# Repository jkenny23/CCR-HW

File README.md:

# CCR v2.5su
Board/schematic/gerber files for the CCR project - v2.5su variant

This variant is the latest (as of 5/6/20) cost optimized version, which supports regen automatically, with use of external buffer pack (clamp circuit limits voltage at input of tester to 12.5V). All specs are the same as v2.4 otherwise (6A charge/discharge symmetric, thermally limited to 21W max without buffer pack). Fixed 2 errors in the v2.4su version, moving TL431 supply to 12V instead of 5V (delay in powering reference caused clamp circuit to engage, shorting power supply if USB power was not provided first), and adding diode to 5V SMPS (MP2359 is a non-synchronous buck whereas v2.4 JW5052C was).

Details here: http://rev0.net/index.php?title=CCR

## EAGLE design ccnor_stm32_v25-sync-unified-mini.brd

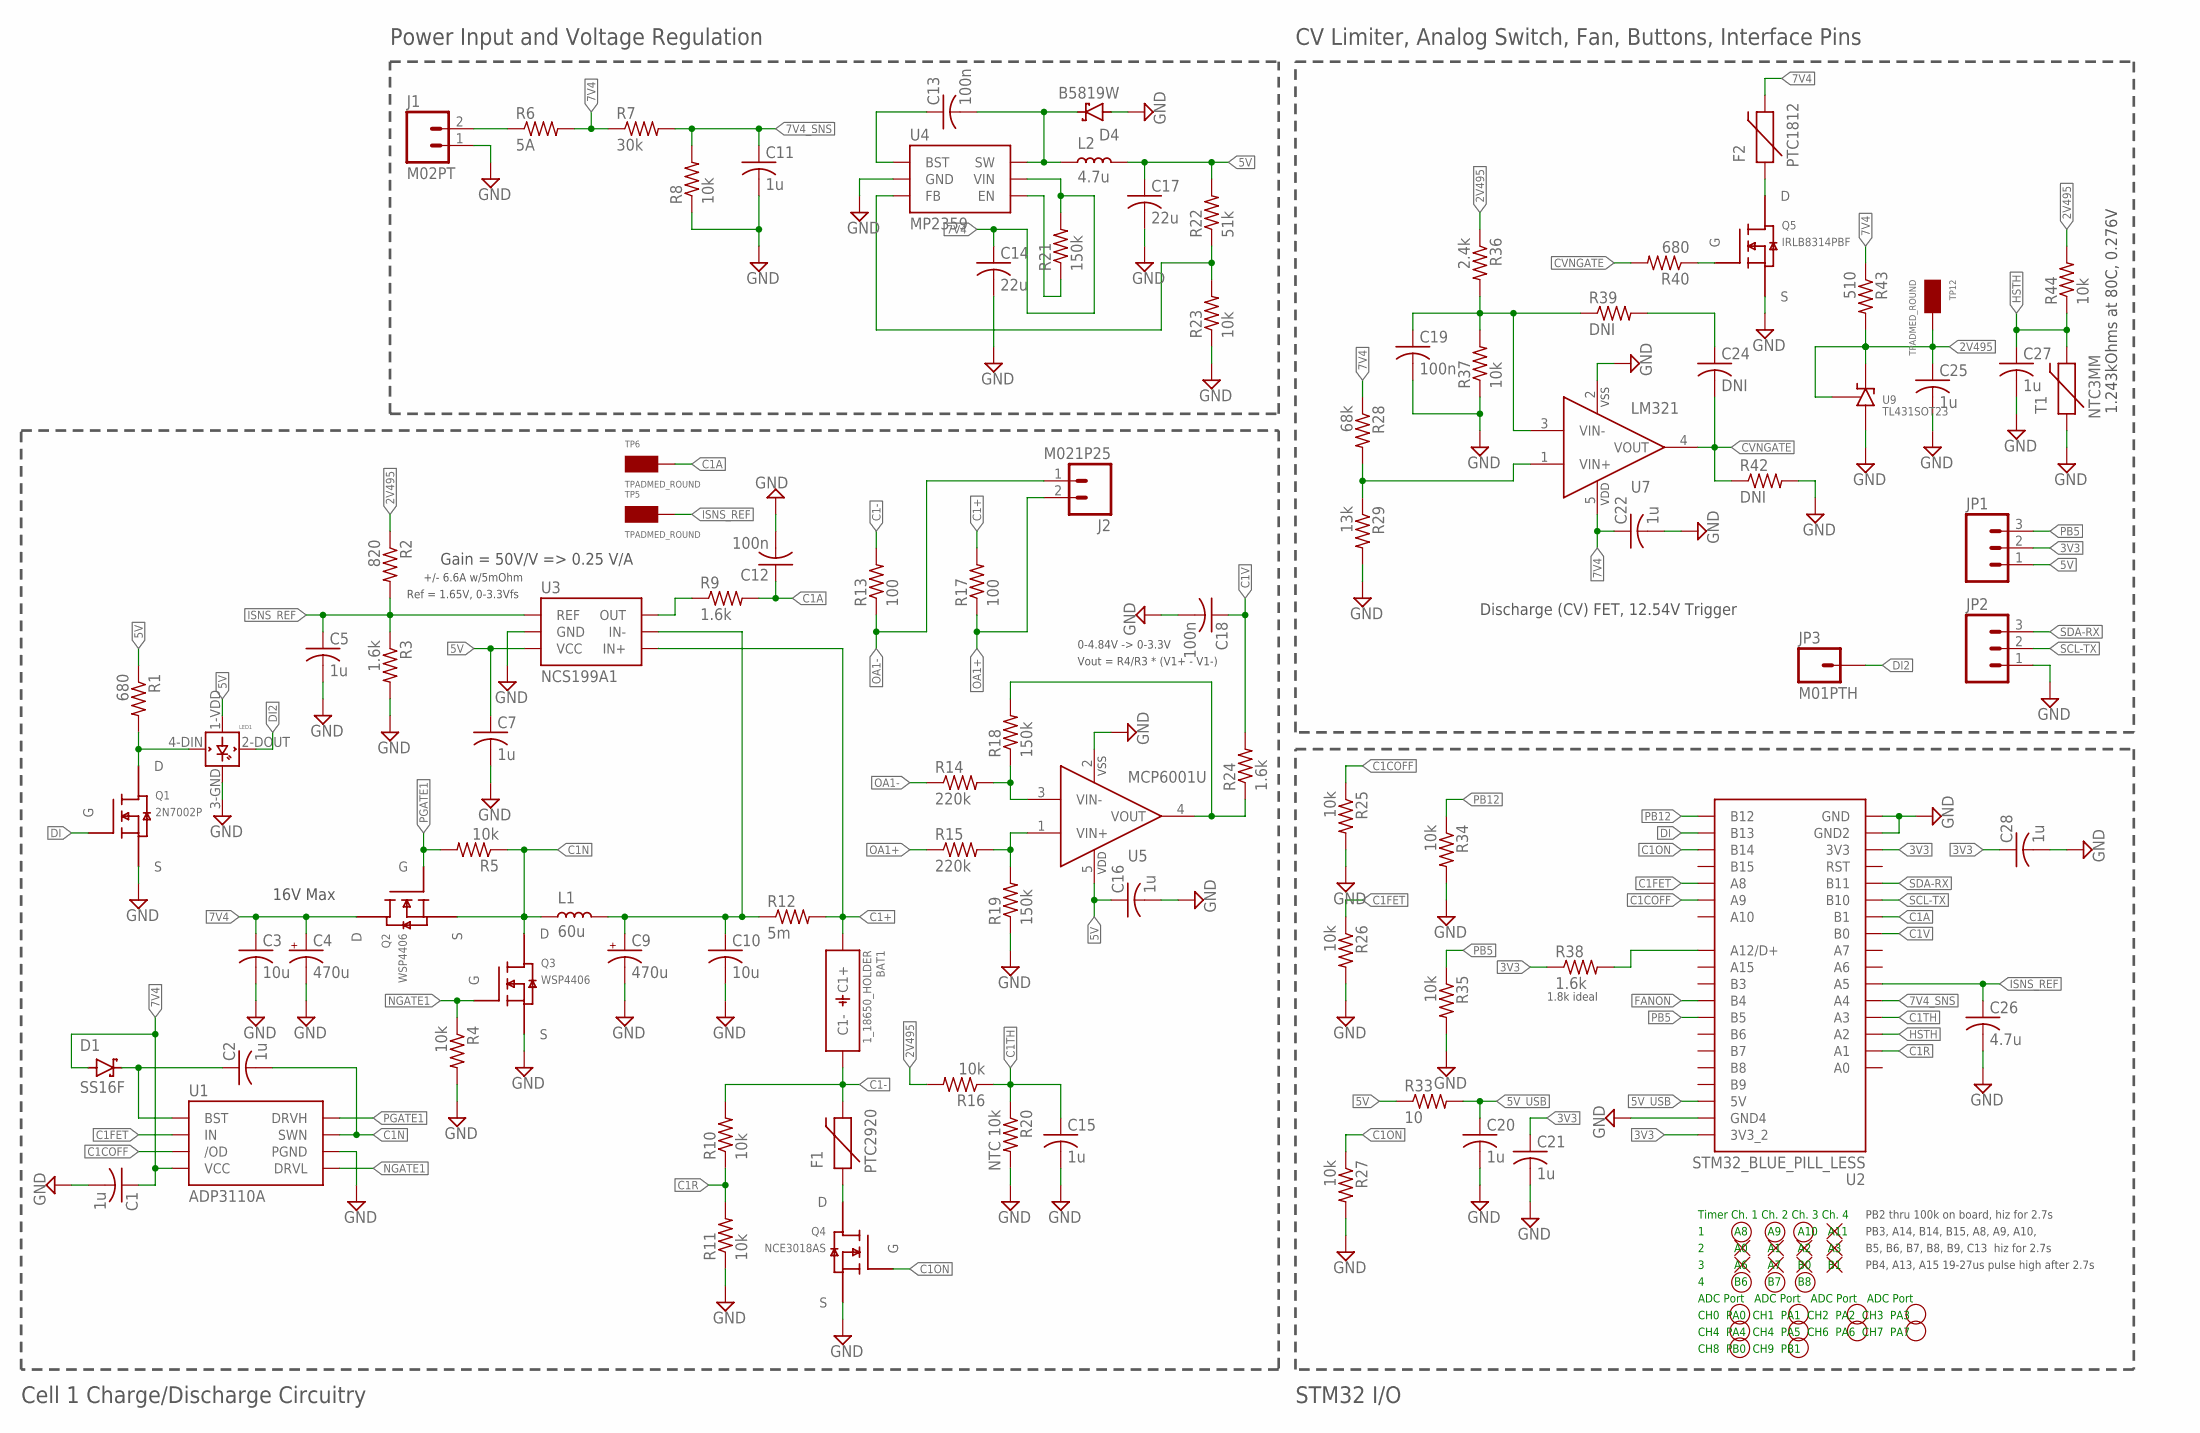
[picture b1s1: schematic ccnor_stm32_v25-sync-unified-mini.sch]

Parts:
BAT1: 1_18650_HOLDER; 1S_18650_SMD_NH
C1, C5, C7, C11, C15, C16, C20, C21, C22, C25, C27, C28: 1u; C0402
C2: 1u; C0603
C3, C10: 10u; C1206
C4, C9: 470u; E2,5-7
C12, C13, C18, C19: 100n; C0402
C14: 22u; C0805
C17: 22u; C0603
C24: DNI; C0402
C26: 4.7u; C0402
D1: SS16F; SOD123
D4: B5819W; SOD123W
F1: PTC2920; 2920
F2: PTC1812; 1812
J1: M02PT; PHOENIXCONTACT1935161
J2: M021P25; M02_1P25MM
JP1, JP2: M03PTH; 1X03
JP3: M01PTH; 1X01
L1: 60u; INDUCTOR_10A_8.2MMX21MM
L2: 4.7u; 0805
LED1: WS2812B
Q1: 2N7002P; SOT23
Q2, Q3: WSP4406; 8-SOIC
Q4: NCE3018AS; 8-SOIC
Q5: IRLB8314PBF; TO-220
R1, R40: 680; R0402
R2: 820; R0402
R3, R9, R24, R38: 1.6k; R0402
R4, R5, R8, R10, R11, R16, R23, R25, R26, R27, R34, R35, R37, R44: 10k; R0402
R6: 5A; R1206
R7: 30k; R0402
R12: 5m; R1206
R13, R17: 100; R0402
R14, R15: 220k; R0402
R18, R19, R21: 150k; R0402
R20: NTC 10k; R0402
R22: 51k; R0402
R28: 68k; R0402
R29: 13k; R0402
R33: 10; R0402
R36: 2.4k; R0402
R39, R42: DNI; R0402
R43: 510; R0402
T1: NTC3MM; THERMISTOR_3MMX3MM
TP5, TP6, TP12: TPADMED_ROUND; TPAD_MED_ROUND
U1: ADP3110A; 8-SOIC
U2: STM32_BLUE_PILL_LESS; STM32_BLUE_PILL_SMD
U3: NCS199A1; SOT-363
U4: MP2359; SOT23-6
U5: MCP6001U; SOT23-5
U7: LM321; SOT23-5
U9: TL431SOT23; SOT23

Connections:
2V495: C25.1, R2.1, R16.2, R36.1, R43.2, R44.2, TP12.1, U9.1 (K), U9.2 (REF)
3V3: C21.1, C28.1, JP1.2, R38.1, U2.3V3, U2.3V3_2
5V: C7.1, C16.1, C17.1, JP1.1, L2.2, LED1.1-VDD (VDD), R1.1, R22.2, R33.1, U3.3 (VCC), U5.5 (VDD)
5V_USB: C20.1, R33.2, U2.5V
7V4: C1.1, C3.1, C4.+, C14.1, C22.1, D1.A (ANODE), F2.2, Q2.5 (D), Q2.6 (D), Q2.7 (D), Q2.8 (D), R6.2, R7.1, R21.2, R28.1, R43.1, U1.4 (VCC), U4.5 (VIN), U7.5 (VDD)
7V4_SNS: C11.1, R7.2, R8.2, U2.A4
BST: C2.1, D1.K (CATHODE), U1.1 (BST)
BST5V: C13.1, U4.1 (BST)
C1+: BAT1.1+ (C1+), R12.2, R17.2, U3.4 (IN+)
C1-: BAT1.1- (C1-), F1.K (2), R10.2, R13.2
C1A: C12.1, R9.2, TP6.1, U2.B1
C1COFF: R25.1, U1.3 (/OD), U2.A9
C1FET: R26.1, U1.2 (IN), U2.A8
C1N: C2.2, L1.P$1, Q2.1 (S), Q2.2 (S), Q2.3 (S), Q3.5 (D), Q3.6 (D), Q3.7 (D), Q3.8 (D), R5.1, U1.7 (SWN)
C1ON: Q4.4 (G), R27.1, U2.B14
C1R: R10.1, R11.2, U2.A1
C1TH: C15.1, R16.1, R20.1, U2.A3
C1V: C18.1, R24.2, U2.B0
C1VFBN: C24.1, R39.2
C1V_OA: R18.2, R24.1, U5.4 (VOUT)
CVNGATE: C24.2, R40.2, R42.1, U7.4 (VOUT)
CVOAREF: C19.1, R36.2, R37.2, R39.1, U7.3 (VIN-)
CVOASNS: R28.2, R29.1, U7.1 (VIN+)
DI: Q1.1 (G), U2.B13
DI1: LED1.4-DIN (DIN), Q1.3 (D), R1.2
DI2: JP3.1, LED1.2-DOUT (DOUT)
EN5V: R21.1, U4.4 (EN)
FANON: U2.B4
FB5V: R22.1, R23.2, U4.3 (FB)
GND: C1.2, C3.2, C4.-, C5.2, C7.2, C9.-, C10.2, C11.2, C12.2, C14.2, C15.2, C16.2, C17.2, C18.2, C19.2, C20.2, C21.2, C22.2, C25.2, C26.2, C27.2, C28.2, D4.A (ANODE), J1.1, JP2.1, LED1.3-GND (GND), Q1.2 (S), Q3.1 (S), Q3.2 (S), Q3.3 (S), Q4.1 (S), Q4.2 (S), Q4.3 (S), Q5.3 (S), R3.2, R4.2, R8.1, R11.1, R19.1, R20.2, R23.1, R25.2, R26.2, R27.2, R29.2, R34.2, R35.2, R37.1, R42.2, T1.1, U1.6 (PGND), U2.GND, U2.GND2, U2.GND4, U3.2 (GND), U4.2 (GND), U5.2 (VSS), U7.2 (VSS), U9.3 (A)
HSTH: C27.1, R44.1, T1.2, U2.A2
IN-1: C9.+, C10.1, L1.P$2, R12.1, U3.5 (IN-)
IS1O: R9.1, U3.6 (OUT)
ISNS_REF: C5.1, C26.1, R2.2, R3.1, TP5.1, U2.A5, U3.1 (REF)
unnamed: R15.2, R19.2, U5.1 (VIN+)
unnamed: R14.2, R18.1, U5.3 (VIN-)
unnamed: F2.1, Q5.2 (D)
unnamed: J1.2, R6.1
unnamed: R38.2, U2.A12 (A12/D+)
unnamed: F1.A (1), Q4.5 (D), Q4.6 (D), Q4.7 (D), Q4.8 (D)
NGATE1: Q3.4 (G), R4.1, U1.5 (DRVL)
OA1+: J2.2, R15.1, R17.1
OA1-: J2.1, R13.1, R14.1
PB5: JP1.3, R35.1, U2.B5
PB12: R34.1, U2.B12
PGATE1: Q2.4 (G), R5.2, U1.8 (DRVH)
Q7G: Q5.1 (G), R40.1
SCL-TX: JP2.2, U2.B10
SDA-RX: JP2.3, U2.B11
SW5V: C13.2, D4.K (CATHODE), L2.1, U4.6 (SW)

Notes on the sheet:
Gain = 50V/V => 0.25 V/A
Ref = 1.65V, 0-3.3Vfs
+/- 6.6A w/5mOhm
Vout = R4/R3 * (V1+ - V1-)
0-4.84V -> 0-3.3V
16V Max
STM32 I/O
Discharge (CV) FET, 12.54V Trigger
Timer Ch. 1 Ch. 2 Ch. 3 Ch. 4
1 A8 A9 A10 A11
2 A0 A1 A2 A3
3 A6 A7 B0 B1
4 B6 B7 B8
ADC Port ADC Port ADC Port ADC Port
CH0 PA0 CH1 PA1 CH2 PA2 CH3 PA3
CH4 PA4 CH4 PA5 CH6 PA6 CH7 PA7
CH8 PB0 CH9 PB1
PB2 thru 100k on board, hiz for 2.7s
PB3, A14, B14, B15, A8, A9, A10,
PB4, A13, A15 19-27us pulse high after 2.7s
B5, B6, B7, B8, B9, C13 hiz for 2.7s
1.243kOhms at 80C, 0.276V
Cell 1 Charge/Discharge Circuitry
CV Limiter, Analog Switch, Fan, Buttons, Interface Pins
1.8k ideal
Power Input and Voltage Regulation

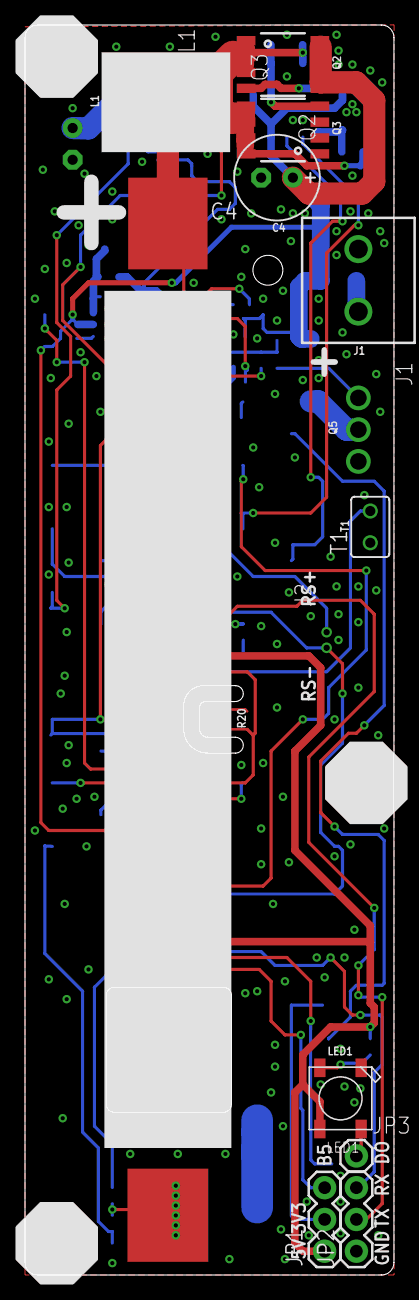
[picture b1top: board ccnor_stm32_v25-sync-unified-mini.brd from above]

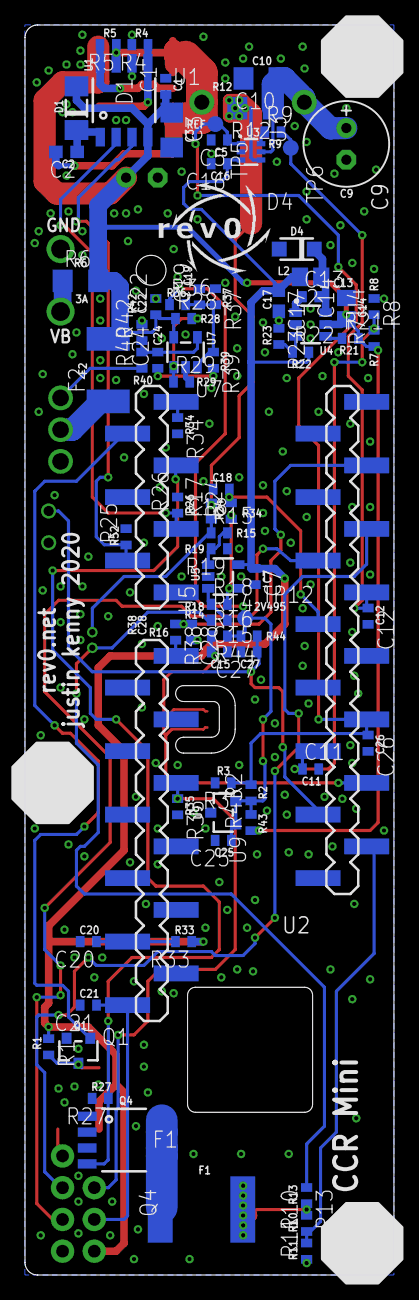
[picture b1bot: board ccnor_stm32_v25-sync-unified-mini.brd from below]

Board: 2 copper layers, 29.5 x 100.0 mm, 94 parts (80 on the bottom side), 49 nets.

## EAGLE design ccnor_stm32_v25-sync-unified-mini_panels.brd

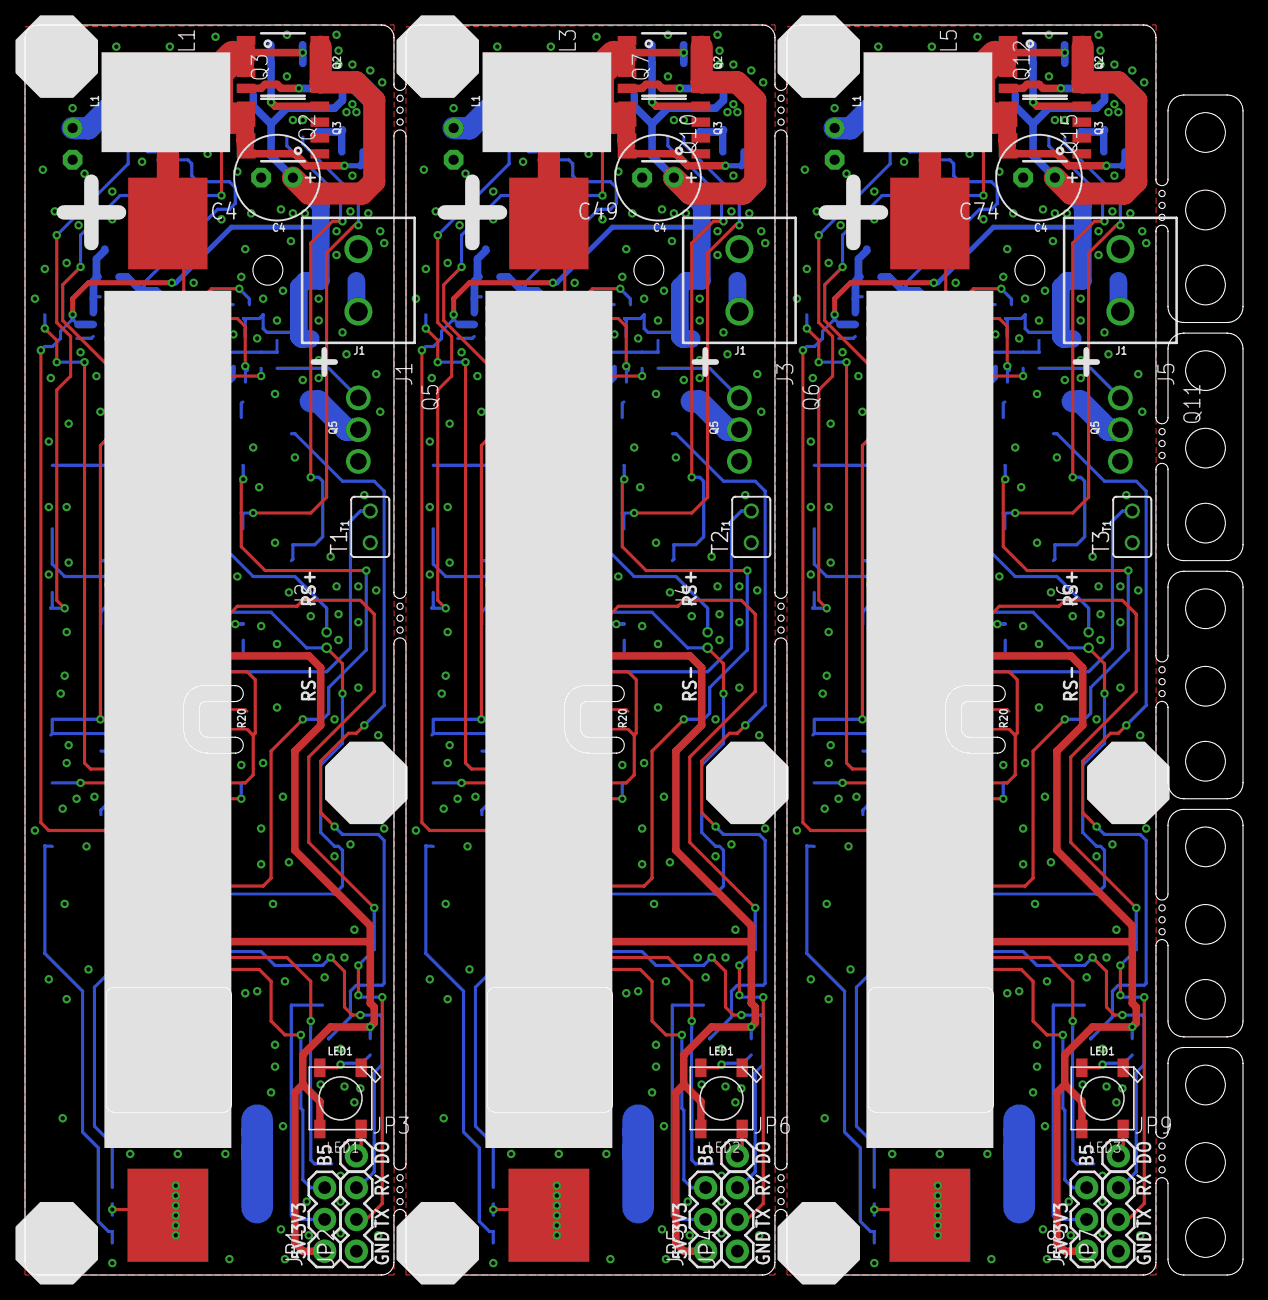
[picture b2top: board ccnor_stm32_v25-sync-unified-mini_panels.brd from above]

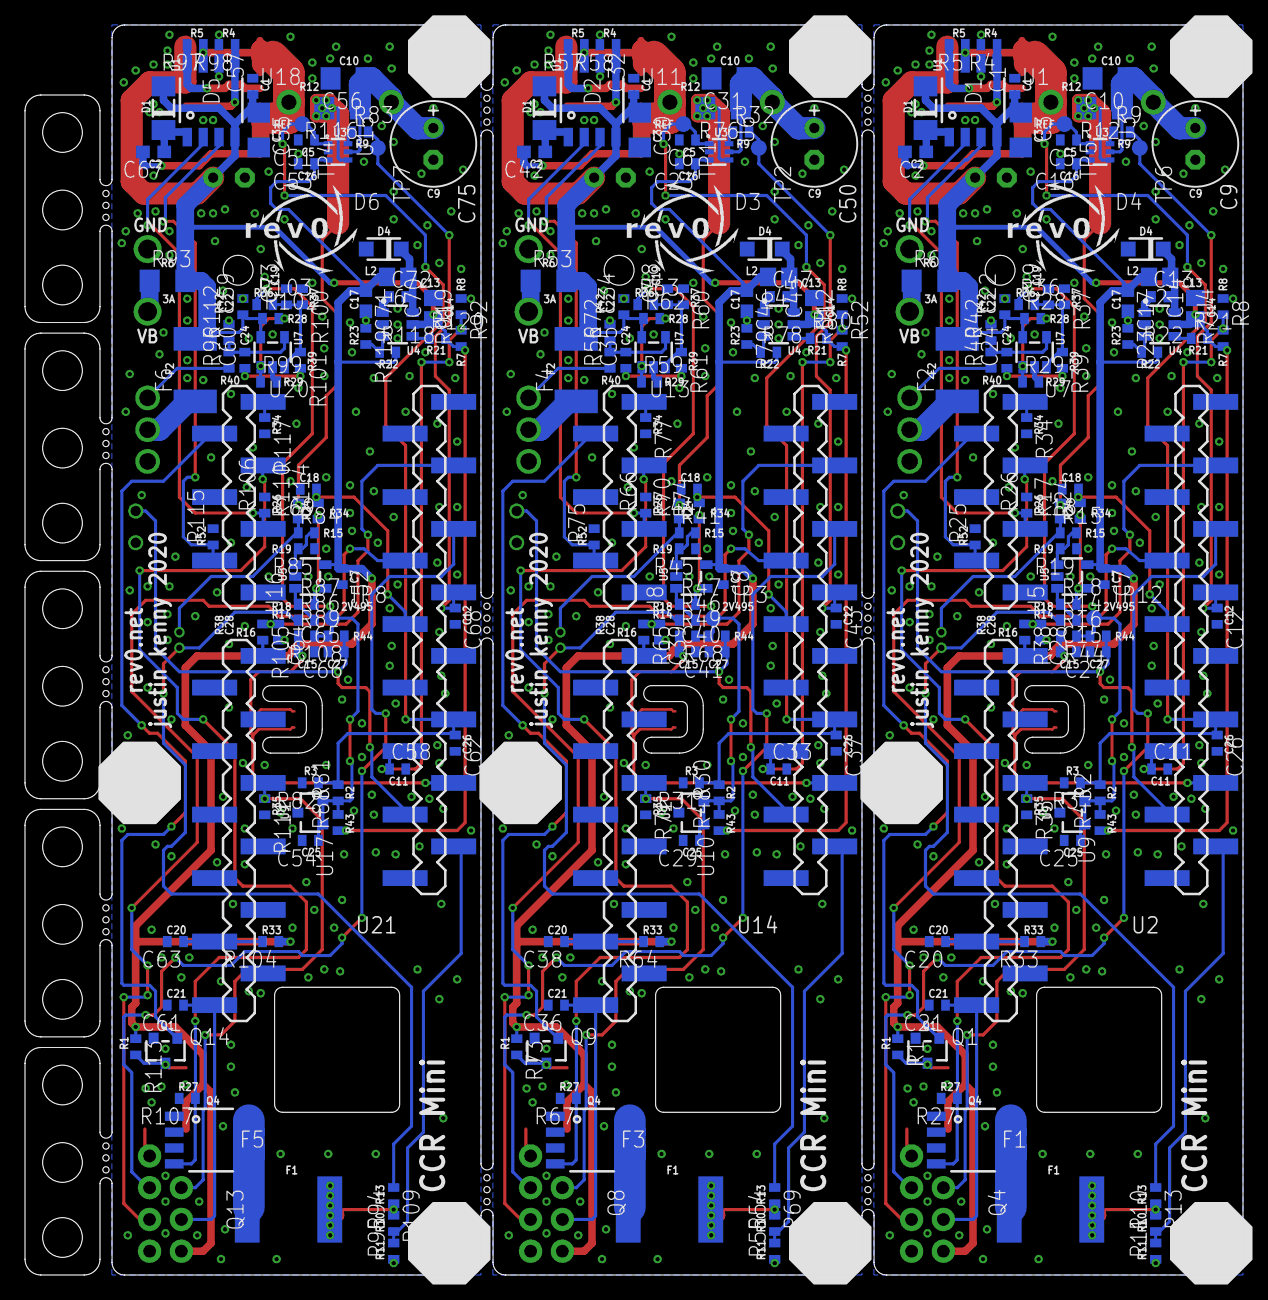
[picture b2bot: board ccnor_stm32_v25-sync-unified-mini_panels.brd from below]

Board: 2 copper layers, 97.4 x 100.0 mm, 282 parts (240 on the bottom side), 147 nets.

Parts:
BAT1, BAT2, BAT3: 1_18650_HOLDER; 1S_18650_SMD_NH
C1, C5, C6, C7, C8, C11, C15, C16, C20, C21, C22, C23, C25, C27, C28, C29, C32, C33, C34, C36, C38, C39, C40, C41, C51, C52, C53, C54, C57, C58, C59, C61, C63, C64, C65, C66: 1u; C0402
C2, C42, C67: 1u; C0603
C3, C10, C30, C31, C55, C56: 10u; C1206
C4, C9, C49, C50, C74, C75: 470u; E2,5-7
C12, C13, C18, C19, C43, C44, C47, C48, C68, C69, C72, C73: 100n; C0402
C14, C45, C70: 22u; C0805
C17, C46, C71: 22u; C0603
C24, C35, C60: DNI; C0402
C26, C37, C62: 4.7u; C0402
D1, D2, D5: SS16F; SOD123
D3, D4, D6: B5819W; SOD123W
F1, F3, F5: PTC2920; 2920
F2, F4, F6: PTC1812; 1812
J1, J3, J5: M02PT; PHOENIXCONTACT1935161
J2, J4, J6: M021P25; M02_1P25MM
JP1, JP2, JP4, JP5, JP7, JP8: 1X03
JP3, JP6, JP9: M01PTH; 1X01
L1, L3, L5: 60u; INDUCTOR_10A_8.2MMX21MM
L2, L4, L6: 4.7u; 0805
LED1, LED2, LED3: WS2812B
Q1, Q9, Q14: 2N7002P; SOT23
Q2, Q3, Q7, Q10, Q12, Q15: WSP4406; 8-SOIC
Q4, Q8, Q13: NCE3018AS; 8-SOIC
Q5, Q6, Q11: IRLB8314PBF; TO-220
R1, R40, R56, R73, R96, R113: 680; R0402
R2, R30, R81: 820; R0402
R3, R9, R24, R31, R32, R38, R65, R74, R82, R83, R105, R114: 1.6k; R0402
R4, R5, R8, R10, R11, R16, R23, R25, R26, R27, R34, R35, R37, R44, R49, R52, R54, R55, R57, R58, R60, R66, R67, R68, R71, R75, R77, R79, R89, R92, R94, R95, R97, R98, R100, R106, R107, R108, R111, R115, R117, R119: 10k; R0402
R6, R53, R93: 5A; R1206
R7, R51, R91: 30k; R0402
R12, R76, R116: 5m; R1206
R13, R17, R69, R70, R109, R110: 100; R0402
R14, R15, R41, R46, R84, R86: 220k; R0402
R18, R19, R21, R45, R47, R80, R85, R87, R120: 150k; R0402
R20, R50, R90: NTC 10k; R0402
R22, R78, R118: 51k; R0402
R28, R62, R102: 68k; R0402
R29, R59, R99: 13k; R0402
R33, R64, R104: 10; R0402
R36, R63, R103: 2.4k; R0402
R39, R42, R61, R72, R101, R112: DNI; R0402
R43, R48, R88: 510; R0402
T1, T2, T3: NTC3MM; THERMISTOR_3MMX3MM
TP1, TP2, TP3, TP4, TP5, TP6, TP7, TP8, TP12: TPADMED_ROUND; TPAD_MED_ROUND
U1, U11, U18: ADP3110A; 8-SOIC
U2, U14, U21: STM32_BLUE_PILL_LESS; STM32_BLUE_PILL_SMD
U3, U6, U15: NCS199A1; SOT-363
U4, U12, U19: MP2359; SOT23-6
U5, U8, U16: MCP6001U; SOT23-5
U7, U13, U20: LM321; SOT23-5
U9, U10, U17: TL431SOT23; SOT23

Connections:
2V1: C29.1, R30.1, R48.2, R49.2, R63.1, R68.2, TP3.1, U10.1, U10.2
2V2: C54.1, R81.1, R88.2, R89.2, R103.1, R108.2, TP8.1, U17.1, U17.2
2V495: C25.1, R2.1, R16.2, R36.1, R43.2, R44.2, TP12.1, U9.1, U9.2
3V1: C36.1, C39.1, JP5.2, R65.1, U14.3V3, U14.3V3_2
3V2: C61.1, C64.1, JP8.2, R105.1, U21.3V3, U21.3V3_2
3V3: C21.1, C28.1, JP1.2, R38.1, U2.3V3, U2.3V3_2
5V: C7.1, C16.1, C17.1, JP1.1, L2.2, LED1.1-VDD, R1.1, R22.2, R33.1, U3.3, U5.5
5V1: C8.1, C23.1, C46.1, JP5.1, L4.2, LED2.1-VDD, R64.1, R73.1, R78.2, U6.3, U8.5
5V2: C52.1, C53.1, C71.1, JP8.1, L6.2, LED3.1-VDD, R104.1, R113.1, R118.2, U15.3, U16.5
5V_USB: C20.1, R33.2, U2.5V
5V_USB1: C38.1, R64.2, U14.5V
5V_USB2: C63.1, R104.2, U21.5V
7V1: C30.1, C32.1, C34.1, C45.1, C49.+, D2.A, F4.2, Q10.5, Q10.6, Q10.7, Q10.8, R48.1, R51.1, R53.2, R62.1, R80.2, U11.4, U12.5, U13.5
7V2: C55.1, C57.1, C59.1, C70.1, C74.+, D5.A, F6.2, Q15.5, Q15.6, Q15.7, Q15.8, R88.1, R91.1, R93.2, R102.1, R120.2, U18.4, U19.5, U20.5
7V4: C1.1, C3.1, C4.+, C14.1, C22.1, D1.A, F2.2, Q2.5, Q2.6, Q2.7, Q2.8, R6.2, R7.1, R21.2, R28.1, R43.1, U1.4, U4.5, U7.5
7V4_SNS: C11.1, R7.2, R8.2, U2.A4
7V4_SNS1: C33.1, R51.2, R52.2, U14.A4
7V4_SNS2: C58.1, R91.2, R92.2, U21.A4
BST: C2.1, D1.K, U1.1
BST1: C42.1, D2.K, U11.1
BST2: C67.1, D5.K, U18.1
BST5V: C13.1, U4.1
BST5V1: C47.1, U12.1
BST5V2: C72.1, U19.1
C1+: BAT1.1+, R12.2, R17.2, U3.4
C1+1: BAT2.1+, R70.2, R76.2, U6.4
C1+2: BAT3.1+, R110.2, R116.2, U15.4
C1-: BAT1.1-, F1.K, R10.2, R13.2
C1-1: BAT2.1-, F3.K, R54.2, R69.2
C1-2: BAT3.1-, F5.K, R94.2, R109.2
C1A: C12.1, R9.2, TP6.1, U2.B1
C1A1: C43.1, R32.2, TP2.1, U14.B1
C1A2: C68.1, R83.2, TP7.1, U21.B1
C1COFF: R25.1, U1.3, U2.A9
C1COFF1: R75.1, U11.3, U14.A9
C1COFF2: R115.1, U18.3, U21.A9
C1FET: R26.1, U1.2, U2.A8
C1FET1: R66.1, U11.2, U14.A8
C1FET2: R106.1, U18.2, U21.A8
C1N: C2.2, L1.P$1, Q2.1, Q2.2, Q2.3, Q3.5, Q3.6, Q3.7, Q3.8, R5.1, U1.7
C1N1: C42.2, L3.P$1, Q7.5, Q7.6, Q7.7, Q7.8, Q10.1, Q10.2, Q10.3, R57.1, U11.7
C1N2: C67.2, L5.P$1, Q12.5, Q12.6, Q12.7, Q12.8, Q15.1, Q15.2, Q15.3, R97.1, U18.7
C1ON: Q4.4, R27.1, U2.B14
C1ON1: Q8.4, R67.1, U14.B14
C1ON2: Q13.4, R107.1, U21.B14
C1R: R10.1, R11.2, U2.A1
C1R1: R54.1, R55.2, U14.A1
C1R2: R94.1, R95.2, U21.A1
C1TH: C15.1, R16.1, R20.1, U2.A3
C1TH1: C40.1, R49.1, R50.1, U14.A3
C1TH2: C65.1, R89.1, R90.1, U21.A3
C1V: C18.1, R24.2, U2.B0
C1V1: C44.1, R74.2, U14.B0
C1V2: C69.1, R114.2, U21.B0
C1VFBN: C24.1, R39.2
C1VFBN1: C35.1, R61.2
C1VFBN2: C60.1, R101.2
C1V_OA: R18.2, R24.1, U5.4
C1V_OA1: R47.2, R74.1, U8.4
C1V_OA2: R87.2, R114.1, U16.4
CVNGATE: C24.2, R40.2, R42.1, U7.4
CVNGATE1: C35.2, R56.2, R72.1, U13.4
CVNGATE2: C60.2, R96.2, R112.1, U20.4
CVOAREF: C19.1, R36.2, R37.2, R39.1, U7.3
CVOAREF1: C48.1, R60.2, R61.1, R63.2, U13.3
CVOAREF2: C73.1, R100.2, R101.1, R103.2, U20.3
CVOASNS: R28.2, R29.1, U7.1
CVOASNS1: R59.1, R62.2, U13.1
CVOASNS2: R99.1, R102.2, U20.1
DI: Q1.1, U2.B13
DI1: LED1.4-DIN, Q1.3, R1.2
DI2: JP3.1, LED1.2-DOUT
DI3: LED2.4-DIN, Q9.3, R73.2
DI4: Q9.1, U14.B13
DI5: JP6.1, LED2.2-DOUT
DI6: LED3.4-DIN, Q14.3, R113.2
DI7: Q14.1, U21.B13
DI8: JP9.1, LED3.2-DOUT
EN5V: R21.1, U4.4
EN5V1: R80.1, U12.4
EN5V2: R120.1, U19.4
FB5V: R22.1, R23.2, U4.3
FB5V1: R78.1, R79.2, U12.3
FB5V2: R118.1, R119.2, U19.3
GND: C1.2, C3.2, C4.-, C5.2, C7.2, C9.-, C10.2, C11.2, C12.2, C14.2, C15.2, C16.2, C17.2, C18.2, C19.2, C20.2, C21.2, C22.2, C25.2, C26.2, C27.2, C28.2, D4.A, J1.1, JP2.1, LED1.3-GND, Q1.2, Q3.1, Q3.2, Q3.3, Q4.1, Q4.2, Q4.3, Q5.3, R3.2, R4.2, R8.1, R11.1, R19.1, R20.2, R23.1, R25.2, R26.2, R27.2, R29.2, R34.2, R35.2, R37.1, R42.2, T1.1, U1.6, U2.GND, U2.GND2, U2.GND4, U3.2, U4.2, U5.2, U7.2, U9.3
GND1: C6.2, C8.2, C23.2, C29.2, C30.2, C31.2, C32.2, C33.2, C34.2, C36.2, C37.2, C38.2, C39.2, C40.2, C41.2, C43.2, C44.2, C45.2, C46.2, C48.2, C49.-, C50.-, D3.A, J3.1, JP4.1, LED2.3-GND, Q6.3, Q7.1, Q7.2, Q7.3, Q8.1, Q8.2, Q8.3, Q9.2, R31.2, R45.1, R50.2, R52.1, R55.1, R58.2, R59.2, R60.1, R66.2, R67.2, R71.2, R72.2, R75.2, R77.2, R79.1, T2.1, U6.2, U8.2, U10.3, U11.6, U12.2, U13.2, U14.GND, U14.GND2, U14.GND4
GND2: C51.2, C52.2, C53.2, C54.2, C55.2, C56.2, C57.2, C58.2, C59.2, C61.2, C62.2, C63.2, C64.2, C65.2, C66.2, C68.2, C69.2, C70.2, C71.2, C73.2, C74.-, C75.-, D6.A, J5.1, JP7.1, LED3.3-GND, Q11.3, Q12.1, Q12.2, Q12.3, Q13.1, Q13.2, Q13.3, Q14.2, R82.2, R85.1, R90.2, R92.1, R95.1, R98.2, R99.2, R100.1, R106.2, R107.2, R111.2, R112.2, R115.2, R117.2, R119.1, T3.1, U15.2, U16.2, U17.3, U18.6, U19.2, U20.2, U21.GND, U21.GND2, U21.GND4
HSTH: C27.1, R44.1, T1.2, U2.A2
HSTH1: C41.1, R68.1, T2.2, U14.A2
HSTH2: C66.1, R108.1, T3.2, U21.A2
IN-1: C9.+, C10.1, L1.P$2, R12.1, U3.5
IN-2: C31.1, C50.+, L3.P$2, R76.1, U6.5
IN-3: C56.1, C75.+, L5.P$2, R116.1, U15.5
IS1O: R9.1, U3.6
IS1O1: R32.1, U6.6
IS1O2: R83.1, U15.6
ISNS_REF: C5.1, C26.1, R2.2, R3.1, TP5.1, U2.A5, U3.1
ISNS_REF1: C6.1, C37.1, R30.2, R31.1, TP1.1, U6.1, U14.A5
ISNS_REF2: C51.1, C62.1, R81.2, R82.1, TP4.1, U15.1, U21.A5
unnamed: R41.2, R45.2, U8.1
unnamed: R46.2, R47.1, U8.3
unnamed: R15.2, R19.2, U5.1
unnamed: R14.2, R18.1, U5.3
unnamed: J3.2, R53.1
unnamed: R65.2, U14.A12
unnamed: F3.A, Q8.5, Q8.6, Q8.7, Q8.8
unnamed: F4.1, Q6.2
unnamed: R84.2, R85.2, U16.1
unnamed: F2.1, Q5.2
unnamed: R86.2, R87.1, U16.3
unnamed: J5.2, R93.1
unnamed: J1.2, R6.1
unnamed: R105.2, U21.A12
unnamed: F5.A, Q13.5, Q13.6, Q13.7, Q13.8
unnamed: F6.1, Q11.2
unnamed: R38.2, U2.A12
unnamed: F1.A, Q4.5, Q4.6, Q4.7, Q4.8
NGATE1: Q3.4, R4.1, U1.5
NGATE2: Q7.4, R58.1, U11.5
NGATE3: Q12.4, R98.1, U18.5
OA1+: J2.2, R15.1, R17.1
OA1+1: J4.2, R41.1, R70.1
OA1+2: J6.2, R84.1, R110.1
OA1-: J2.1, R13.1, R14.1
OA1-1: J4.1, R46.1, R69.1
OA1-2: J6.1, R86.1, R109.1
PB1: JP5.3, R71.1, U14.B5
PB2: R77.1, U14.B12
PB3: JP8.3, R111.1, U21.B5
PB4: R117.1, U21.B12
PB5: JP1.3, R35.1, U2.B5
PB12: R34.1, U2.B12
PGATE1: Q2.4, R5.2, U1.8
PGATE2: Q10.4, R57.2, U11.8
PGATE3: Q15.4, R97.2, U18.8
Q7G: Q5.1, R40.1
Q7G1: Q6.1, R56.1
Q7G2: Q11.1, R96.1
SCL-TX: JP2.2, U2.B10
SCL-TX1: JP4.2, U14.B10
SCL-TX2: JP7.2, U21.B10
SDA-RX: JP2.3, U2.B11
SDA-RX1: JP4.3, U14.B11
SDA-RX2: JP7.3, U21.B11
SW5V: C13.2, D4.K, L2.1, U4.6
SW5V1: C47.2, D3.K, L4.1, U12.6
SW5V2: C72.2, D6.K, L6.1, U19.6

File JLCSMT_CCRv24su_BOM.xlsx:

Comment | Designator | Footprint | LCSC Part #（optional）
1.6k | R3, R9, R24, R38, R47, R59 | 0402_R | C4908 | ext
1u | C1, C2, C5, C6, C7, C8, C11, C15, C16, C20, C21, C22, C23, C25, C27, C28, C29, 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 | 0402_C | C52923
2.4k | R36 | 0402_R | C25882
2N7002P | Q1 | SOT-23 | C8545
4.7u | C26 | 0402_C | C23733
4.7u | L2 | 0805_L | C86088 | ext
5m | R12, R50 | 1206_R | C76290 | ext
10 | R33 | 0402_R | C25077
10k | R4, R5, R8, R10, R11, R16, R23, R25, R26, R27, R30, R31, R32, R34, R35, R37, R4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 | 0402_R | C25744
10u | C3, C10, C31, C36 | 1206_C | C15850
13k | R29 | 0402_R | C22797
22u | C17 | 0603_C | C59461
22u | C14 | 0805_C | C45783
30k | R7 | 0402_R | C22984
68k | R28 | 0402_R | C36871
100 | R13, R17, R51, R55 | 0402_R | C25076
100n | C12, C13, C18, C19, C37, C40 | 0402_C | C1525
51k | R22 | 0402_R | C25794
120 | R43 | 0402_R | C25079
150k | R18, R19, R21, R56, R57 | 0402_R | C25755
220k | R14, R15, R52, R53 | 0402_R | C25969
680 | R1, R40 | 0402_R | C25130
820 | R2 | 0402_R | C23253
Tactile Switch | S1, S2 | 5.05x5.05mm | C318884 | ext
AO3400A | Q6 | SOT-23 | C20917
3.3V | U2 | SOT-89 | C73287 | ext
ADP3110A | U1, U10 | SOIC-8 | C82321 | ext
MP2359 | U4 | SOT-23-6 | C14259
LM321 | U7 | SOT-23-6 | C97688 | ext
MCP6001U | U5, U12 | SOT-23-6 | C21403 | ext
NCE3018AS | Q4, Q9 | SOIC-8 | C163739 | ext
NCS199A1 | U3, U11 | SC-70-6 | C179595 | ext
NTC 10k | R20, R58 | 0402_R | C77131 | ext
PTC2920 | F1, F2, F3 | 2920_R | C207091 | ext
SN74LVC1G3157SC70-6 | U6 | SC-70-6 | C38663 | ext
SS16F | D1, D3 | SOD-123 | C8598
SS54 | D2 | SMA | C22452
TL431SOT23 | U9 | SOT-23 | C3113
WS2812B | LED1, LED2 | 4-SMD | C114586 | ext

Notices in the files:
parts and their libraries:
SparkFun: Licensing: CC v3.0 Share-Alike You are welcome to use this library for commercial purposes.
